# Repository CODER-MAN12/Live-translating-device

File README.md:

The **firmware is currently in development** and will be published to this repository as soon as it is ready. But for now there is a demo code
THE CODE RIGHT NOW IS AI Because i am still learning how to code hardware stuff!!!!!!!!!!!!!!!!!!!!!!!

##  Roadmap & Current Status

 Initial hardware concept design
 CAS/CAD modeling and assembly validation
 Generate production-ready publish files
 **Firmware development (In Progress)**
 Integration testing and final release

##  Bill of Materials (BOM)

| Part | Qty | Unit | Total | Vendor | Link |
| :--- | :---: | :---: | :---: | :--- | :--- |
| AudioJack2 | 1 | $0.50 | $0.50 | DigiKey | [Link](https://www.digikey.com/en/products/filter/audio-jacks/394) |
| Adafruit Micro-Lipo | 1 | $5.95 | $5.95 | Adafruit | [Link]([https://www.adafruit.com/product/1904](https://www.aliexpress.com/item/1005013135521530.html?spm=a2g0o.cart.0.0.6d8038daVLqc9C&mp=1&pdp_npi=6%40dis%21CAD%21CAD+13.08%21CAD+11.38%21%21CAD+11.38%21%21%21%40210327ef17947724709084493e0d19%2112000060381158609%21ct%21CA%218455289665%21%211%210%21) |
| Speaker | 1 | $3.95 | $3.95 | Adafruit | [Link](https://www.adafruit.com/product/3923) |
| SPH0645LM4H | 1 | $6.95 | $6.95 | Adafruit | [Link](https://www.adafruit.com/product/3421) |
| R 10k | 5 | $0.05 | $0.25 | DigiKey | [Link](https://www.digikey.com/en/products/detail/yageo/RC0805JR-0710KL/727282) |
| SW_Nidec_CAS-120A1 | 1 | $0.85 | $0.85 | DigiKey | [Link](https://www.digikey.com/en/products/detail/nidec-components-corporation/CAS-120A1/1004126) |
| ESP32-S3-WROOM-2 | 1 | $3.80 | $3.80 | DigiKey | [Link](https://www.digikey.com/en/products/detail/espressif-systems/ESP32-S3-WROOM-1-N8/15200089) |
| ER_OLEDM0.91_1x-I2C | 1 | $3.50 | $3.50 | BuyDisplay | [Link](https://www.buydisplay.com/default/0-91-inch-128x32-oled-display-module-i2c-serial-spi) |
| AP2112K-3.3 | 1 | $0.45 | $0.45 | DigiKey | [Link](https://www.digikey.com/en/products/detail/diodes-incorporated/AP2112K-3-3TRG1/4470746) |
| MAX98357A | 1 | $5.95 | $5.95 | Adafruit | [Link](https://www.adafruit.com/product/3006) |
| PCM5102A | 1 | $4.00 | $4.00 | Amazon | [Link](https://www.amazon.com/dp/B07Q6S8SFL) |
| PCBWay Prototype PCB (5-pack) | 1 | $55.00 | $55.00 | PCBWay | [Link](https://www.pcbway.com/orderonline.aspx) |

ALSO MY CART IS ONLY LESS THAN 100 DOLLARS BECAUSE PCB- WAY DIDNT GIVE ME THE PRCES OF THE PARTS YET !!!!!!!!!!!!!!

BTW ALSO YOU NEED TO BUY THE ADAFRUIT MICRO LIPO BATTERY CHAGER BECAUSE I WILL SOLDER IT ON MY SELF ON TO A 5 PIN HEADER

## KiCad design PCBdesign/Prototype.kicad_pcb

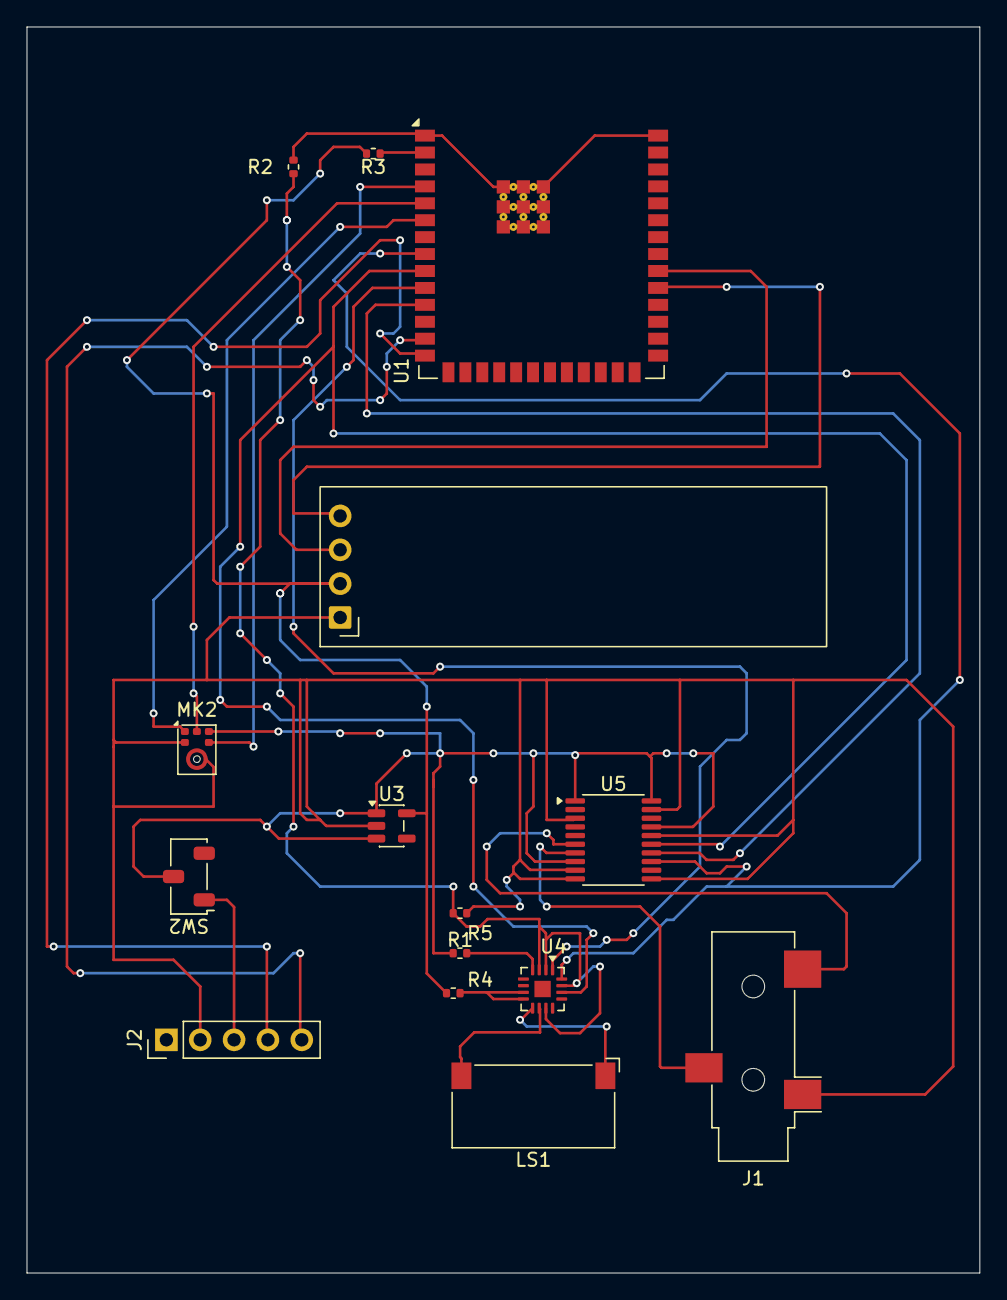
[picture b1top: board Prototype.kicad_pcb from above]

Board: 2 copper layers, 71.5 x 93.5 mm, 15 parts (0 on the bottom side), 24 nets.

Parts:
J1: AudioJack2; Jack_3.5mm_CUI_SJ-3523-SMT_Horizontal
J2: Adafruit Micro-Lipo; PinHeader_1x05_P2.54mm_Vertical
LS1: Speaker; Speaker_CUI_CMR-1206S-67
MK2: SPH0645LM4H; Knowles_SPH0645LM4H-6_3.5x2.65mm
R1, R2, R3, R4, R5: R 10k; R_0402_1005Metric
SW2: SW_Nidec_CAS-120A1; Nidec_Copal_CAS-120A
U1: ESP32-S3-WROOM-2
U2: ER_OLEDM0.91_1x-I2C
U3: AP2112K-3.3; SOT-23-5
U4: MAX98357A; TQFN-16-1EP_3x3mm_P0.5mm_EP1.23x1.23mm
U5: PCM5102A; TSSOP-20_4.4x6.5mm_P0.65mm

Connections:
unnamed: J2.BAT (BAT_3), SW2.1 (C)
unnamed: J2.D+ (D+_4), U1.14 (USB_D+/IO20)
unnamed: J2.D- (D-_5), U1.13 (USB_D-/IO19)
unnamed: J1.S, J2.GND (GND_2), MK2.2 (SEL), MK2.3 (GND), R5.1, U2.1 (GND), U3.2 (GND), U5.3 (CPGND), U5.9 (AGND), U5.10 (DEMP), U5.11 (FLT), U5.16 (FMT), U5.19 (DGND)
unnamed: MK2.4 (BCLK), U1.4 (IO4)
unnamed: MK2.6 (DATA), U1.5 (IO5)
unnamed: MK2.5 (VDD), R1.1, SW2.2 (B), U3.1 (VIN), U3.3 (EN), U5.1 (CPVDD), U5.8 (AVDD), U5.17 (XSMT), U5.20 (DVDD)
unnamed: MK2.1 (WS), U1.6 (IO6)
unnamed: R2.2, U1.1 (GND), U1.40 (GND), U1.41 (GND)
unnamed: R4.1, U4.7 (VDD), U4.8 (VDD)
unnamed: R3.2, U1.2 (3V3)
unnamed: U1.8 (IO15), U4.16 (BCLK), U5.13 (BCK)
unnamed: U1.9 (IO16), U4.14 (LRCLK), U5.15 (LRCK)
unnamed: U1.10 (IO17), U4.1 (DIN)
unnamed: U1.11 (IO18), U5.14 (DIN)
unnamed: U1.31 (IO38), U2.4 (SDA)
unnamed: U1.32 (MTCK/IO39), U2.3 (SCL)
unnamed: R3.1, R4.2, U2.2 (VCC), U3.5 (VOUT)
unnamed: R2.1, R5.2, U4.2 (GAIN_SLOT), U4.3 (GND), U4.11 (GND), U4.15 (GND)
unnamed: LS1.2, U4.10 (OUTN)
unnamed: LS1.1, U4.9 (OUTP)
unnamed: R1.2, U4.4 (~SD_MODE)
unnamed: J1.T, U5.6 (OUTL)
unnamed: J1.R, U5.7 (OUTR)

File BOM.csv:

Item,Qty,Supplier,Cost/item,Total Cost,link
AudioJack2,1,DigiKey,$0.50,$0.50,https://www.digikey.com/en/products/filter/audio-jacks/394
Adafruit Micro-Lipo,1,Adafruit,$5.95,$5.95,https://www.adafruit.com/product/1904
Speaker,1,Adafruit,$3.95,$3.95,https://www.adafruit.com/product/3923
SPH0645LM4H,1,Adafruit,$6.95,$6.95,https://www.adafruit.com/product/3421
R 10k,5,DigiKey,$0.05,$0.25,https://www.digikey.com/en/products/detail/yageo/RC0805JR-07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
SW_Nidec_CAS-120A1,1,DigiKey,$0.85,$0.85,https://www.digikey.com/en/products/detail/nidec-components-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
ESP32-S3-WROOM-2,1,DigiKey,$3.80,$3.80,https://www.digikey.com/en/products/detail/espressif-systems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
ER_OLEDM0.91_1x-I2C,1,BuyDisplay,$3.50,$3.50,https://www.buydisplay.com/default/0-91-inch-128x32-oled-dis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
AP2112K-3.3,1,DigiKey,$0.45,$0.45,https://www.digikey.com/en/products/detail/diodes-incorporat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
MAX98357A,1,Adafruit,$5.95,$5.95,https://www.adafruit.com/product/3006
PCM5102A,1,Amazon,$4.00,$4.00,https://www.amazon.com/dp/B07Q6S8SFL
PCBWay Prototype PCB (5-pack),1,PCBWay,$55.00,$55.00,https://www.pcbway.com/orderonline.aspx
Estimated total shipping,1,,,$75.00,
